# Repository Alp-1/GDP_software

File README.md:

This project aims to develop a rover that can navigate through different terrain in a forest environment autonomously.
The wiki containing more informatin about the rover can be found [here](https://github.com/Alp-1/NANA-Forest-Rover/wiki).

A more detailed account of the development process can be found [here](https://alportakci.com/projects/).

## The directory layout

    .
    ├── .vscode                 # VS Code settings
    ├── CAD Models              # CAD Models used in the project with attributions. 
    ├── ESP32                   # ESP32 code for ESP32-C3 dronebridge.
    ├── GPS                     # Script to start NTRIP caster.
    ├── low_level_control       # Low level control
    ├── lua_scripts             # Lua scripts uploaded in flight controller
    ├── navigation              # Autonomous navigation
    ├── pyrealsense             # Intel Realsense library required on Raspberry Pi
    ├── schematic               # Schematic of the low level controller
    ├── .gitignore
    ├── pyproject.toml          # Python dependencies
    └── README.md

### Installation
To run some code that are not hardware dependent on your local PC, you can run the following commands in Python (Version used: **3.10.5** in PC and Raspberry Pi):

(./ is the repo root directory)
```sh
$ pip install -e .
```

## Low Level Control
There are two components in the low level control i.e. the motor controller and the central hub. They are both implemented on the Raspberry Pi Pico using micropython. See the [README.md](low_level_control/README.md) in the low level control folder for more information.

## Autonomous navigation
The files in the pyrealsense folder may have to be in the same directory as the navigation scripts, depending on your installation.
Another option is to include the right package from local directory i.e. 
```python
from pyrealsense import pyrealsense2 as rs
``` 
To run the autonomous navigation script, use the following command in the navigation folder:
```sh
$ python navigation_final.py
```
## Research Poster

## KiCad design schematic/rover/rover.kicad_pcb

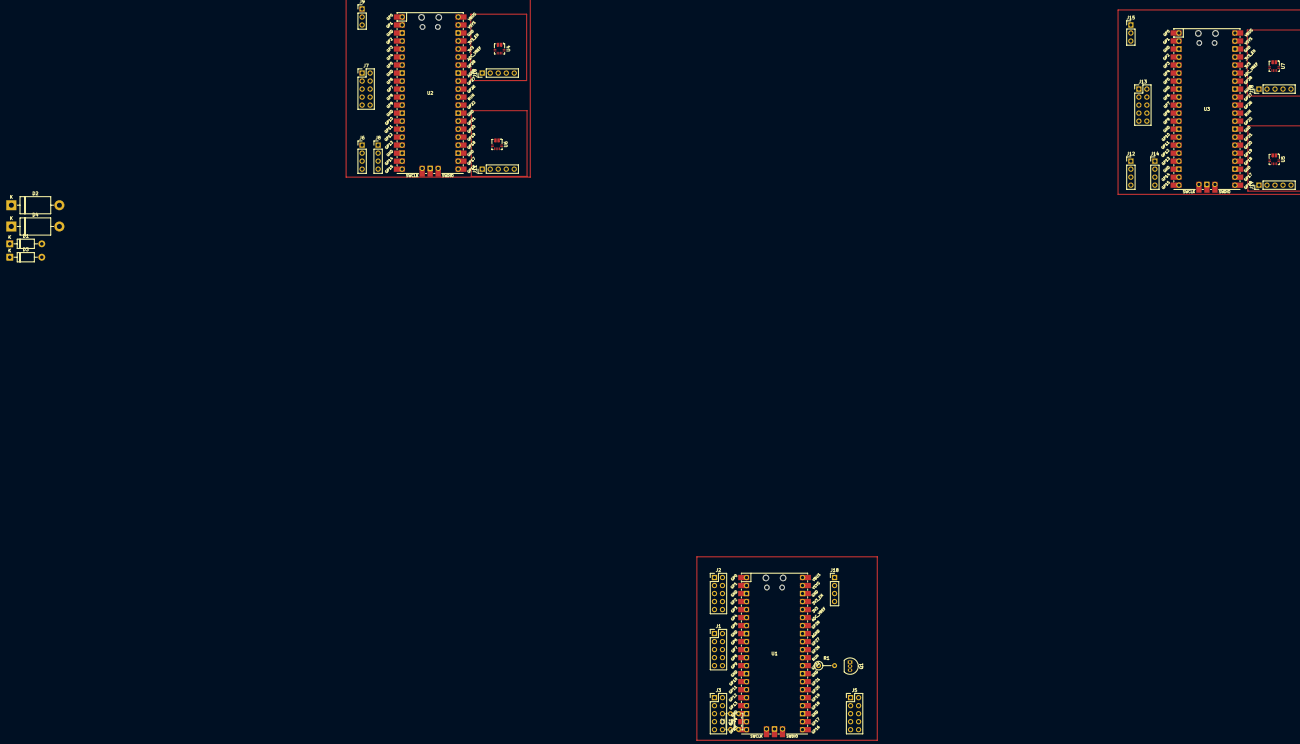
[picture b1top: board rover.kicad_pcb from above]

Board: 2 copper layers, 32 parts (0 on the bottom side), 34 nets, no tracks yet.

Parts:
C1, C2: 3.3n; C_Disc_D5.0mm_W2.5mm_P5.00mm
D1, D3: 1N4733A; D_DO-41_SOD81_P10.16mm_Horizontal
D2, D4: 1N5820; D_DO-201AD_P15.24mm_Horizontal
J1: Front_Wheel_Conn; PinHeader_2x05_P2.54mm_Vertical
J2: Rear_Wheel_Conn; PinHeader_2x05_P2.54mm_Vertical
J3: Flight_Controller_Conn; PinHeader_2x05_P2.54mm_Vertical
J5: Receiver_Conn; PinHeader_2x05_P2.54mm_Vertical
J6, J12: Left_Encoder; PinHeader_1x04_P2.54mm_Vertical
J7, J13: Conn_02x05_Odd_Even; PinHeader_2x05_P2.54mm_Vertical
J8, J14: Right_Encoder; PinHeader_1x04_P2.54mm_Vertical
J9, J15: Conn_01x03_Socket; PinHeader_1x03_P2.54mm_Vertical
J10, J16: Right_Current_Sense; PinHeader_1x05_P2.54mm_Vertical
J11, J17: Left_Current_Sense; PinHeader_1x05_P2.54mm_Vertical
J18: Conn_01x04_Socket; PinHeader_1x04_P2.54mm_Vertical
Q1: BC547; TO-92_Inline
R1: 100k; R_Axial_DIN0207_L6.3mm_D2.5mm_P5.08mm_Vertical
U1, U2, U3: Pico; RPi_Pico_SMD_TH
U4, U5, U6, U7: ACS711xEXLT-31AB; Allegro_QFN-12-10-1EP_3x3mm_P0.5mm

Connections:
+3.3V: J5.3, J6.3, J8.3, J10.3, J11.3, J12.3, J14.3, J16.3, J17.3, U1.36 (3V3), U2.36 (3V3), U3.36 (3V3), U4.10 (VCC), U5.10 (VCC), U6.10 (VCC), U7.10 (VCC)
+5V: J9.1, J15.1, J18.2, U1.39 (VSYS)
/low level control/+5V_in: D2.1 (K), U2.39 (VSYS), U3.39 (VSYS)
/low level control/Sabertooth_front/S1: J9.2, U2.1 (GPIO0)
/low level control/Sabertooth_front/S2: J18.4, Q1.1 (C)
/low level control/Sabertooth_rear/S1: J15.2, U3.1 (GPIO0)
/low level control/central_hub/FC__SBUS: J3.1, J5.1
/low level control/central_hub/FC__Throttle_Left: C1.1, J3.8, U1.19 (GPIO14)
/low level control/central_hub/FC__Throttle_Right: C2.1, J3.10, U1.20 (GPIO15)
/low level control/central_hub/Flight_Controller__RX: J3.7, U1.22 (GPIO17)
/low level control/central_hub/Flight_Controller__TX: J3.9, U1.21 (GPIO16)
/low level control/central_hub/Front_Controller__RX: J1.8, J7.8, U1.2 (GPIO1), U2.6 (GPIO4)
/low level control/central_hub/Front_Controller__TX: J1.10, J7.10, U1.1 (GPIO0), U2.7 (GPIO5)
/low level control/central_hub/NeoPixelRGB: J18.1, U1.32 (GPIO27_ADC1)
/low level control/central_hub/OUTA_Left__Front: J1.7, J6.4, J7.7, U1.7 (GPIO5), U2.16 (GPIO12)
/low level control/central_hub/OUTA_Left__Rear: J2.7, J3.3, J12.4, J13.7, U1.14 (GPIO10), U3.16 (GPIO12)
/low level control/central_hub/OUTA_Right__Front: J1.6, J7.6, J8.4, U1.5 (GPIO3), U2.20 (GPIO15)
/low level control/central_hub/OUTA_Right__Rear: J2.6, J3.4, J13.6, J14.4, U1.17 (GPIO13), U3.20 (GPIO15)
/low level control/central_hub/OUTB_Left__Front: J1.9, J6.1, J7.9, U1.6 (GPIO4), U2.17 (GPIO13)
/low level control/central_hub/OUTB_Left__Rear: J2.9, J3.5, J12.1, J13.9, U1.15 (GPIO11), U3.17 (GPIO13)
/low level control/central_hub/OUTB_Right__Front: J1.4, J7.4, J8.1, U1.4 (GPIO2), U2.19 (GPIO14)
/low level control/central_hub/OUTB_Right__Rear: J2.4, J3.2, J13.4, J14.1, U1.16 (GPIO12), U3.19 (GPIO14)
/low level control/central_hub/Rear_Controller__RX: J2.8, J13.8, U1.12 (GPIO9), U3.6 (GPIO4)
/low level control/central_hub/Rear_Controller__TX: J2.10, J13.10, U1.11 (GPIO8), U3.7 (GPIO5)
/low level control/central_hub/Receiver__PPM: J5.2, U1.27 (GPIO21)
/power supply/5V_RaspberryPi: D3.1 (K), D4.2 (A)
GND: C1.2, C2.2, D1.2 (A), D3.2 (A), J1.2, J2.2, J3.6, J5.5, J6.2, J7.2, J8.2, J9.3, J10.1, J10.2, J11.1, J11.2, J12.2, J13.2, J14.2, J15.3, J16.1, J16.2, J17.1, J17.2, J18.3, Q1.3 (E), U1.3 (GND), U1.8 (GND), U1.13 (GND), U1.18 (GND), U1.23 (GND), U1.28 (GND), U1.38 (GND), U2.3 (GND), U2.18 (GND), U2.23 (GND), U2.28 (GND), U2.38 (GND), U3.3 (GND), U3.18 (GND), U3.23 (GND), U3.28 (GND), U3.38 (GND), U4.3 (GND), U5.3 (GND), U6.3 (GND), U7.3 (GND)
unnamed: D1.1 (K), D2.2 (A)
unnamed: J10.4, U2.32 (GPIO27_ADC1), U6.9 (VIOUT)
unnamed: J11.4, U2.34 (GPIO28_ADC2), U4.9 (VIOUT)
unnamed: J16.4, U3.32 (GPIO27_ADC1), U7.9 (VIOUT)
unnamed: J17.4, U3.34 (GPIO28_ADC2), U5.9 (VIOUT)
unnamed: Q1.2 (B), R1.2
unnamed: R1.1, U1.29 (GPIO22)

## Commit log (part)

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2023-10-30 encoder
2023-11-08 added basic depth based obstacle avoidance
2023-11-10 Motor controller
2023-11-20 Update 2 files
    - /GPS/gnssapp.py
    - /GPS/messntripcomms.py
2023-11-22 Copy dronebridge repo from https://github.com/DroneBridge/ESP32
2023-11-22 Changes to the code to establish serail over UART on ESP32C3
    Changes to the UART port (2 ->1), changes to the proxy, "1604",
2023-11-22 Rebuilding the project
2023-11-22 Changes to the UART pin assignment, to receive information flight controller
2023-11-24 added a simple version of the obstacle avoidance algorithm
2023-11-26 debugging navigation integration
2023-11-26 override rc channels
2023-11-27 commented out things
2023-11-28 added data collection script
2023-12-03 changed the camera settings to reduce motion blur
2023-12-03 changed camera settings for steering
2023-12-03 mode switching
2023-12-03 bugfixing
2023-12-04 fuck
2023-12-04 Add some essential mavlink message handler to give:
    - voltage
    - current
    - speed
    - encode,current data from pico
2023-12-05 Enable current readings from pico to Flight controller
    - Refactor communication methods between cntral hub and controller to use the standardised protocol
2023-12-05 Add standardised protocol for interpico comms
    - Required to allow current values to be passed between picos
2023-12-05 Update tests to use the latest protocols
2023-12-05 Add Software serial class
    - Required for communication with FC as exsiting 2 uarts are insufficient
2023-12-05 Add limits for negative values coming from pulse timeout
2023-12-05 Update code for stripboard layout
    - Receiver - Changed for more compact layout
    - Central_UART -Changed due to GND shorted with 8/9 pin pair
2023-12-05 Fix uart bug in mavlite that initialises with default pin
2023-12-05 Add mavlink library from MavLite
    - Add upy_mavlink package
2023-12-05 Refactor protocol.py
    - Update the protocol with the latest set of command types
    - Make protocol more robust by accumulating and slicing data instead of hoping for timing sync
    - Creates two buffer as central hub requires two sets of separate buffer for messages coming from front and rear
2023-12-05 Refactor motor_controller
    - Remove handshake together with the changes in central_hub
    - Add constant sensor data broadcast methods
    - Commented out pid as it is not stable yet
2023-12-05 Chnage central_hub to match latest mavlink implementation
    - Use asyncio for main loop in central hub
    - Respond to sensor data instead of requesting them to reduce chances of failure
    - Scrape handshake wait as it does not contribute much at the moment
    - The driver can be put to disable by just sending drive(0,0) or e-stop
2023-12-05 Reduce baudrate for softuart to reduce the load on pico
    - Reduce the lost packets as well
2023-12-05 Allow PID to be stopped in deadzone
    - Further tune PID constants for period of 200ms
2023-12-05 Replace Exception with bounded input
2023-12-05 Add methods to check the status of receiver and encoder
2023-12-05 Remove exit fault code as the state is updated in parse_command
2023-12-05 Increase the pulse timeout for pwm
    - Ensure the pulse is captured by the pico
2023-12-05 Update hardware change in the pins
    - The estop becomes active high because of the transistor switching circuit
2023-12-05 Make speed and turn input reversible in direct rc mode
2023-12-05 Prevent hardware interrupt firing before memory allocation
2023-12-05 Refactor state handler to configure state in parse command
2023-12-05 Increase sensor update rate, pid output range and deadzone
    - Fix typo and remove unused code
2023-12-05 Modify PPR
    - Formula: gear ratio * motor PPR * 4 (51*12*4=2448)
2023-12-05 added simple avoidance for testing
2023-12-05 what
2023-12-05 final testing
2023-12-05 Implement clipping output instead of driving to 0 immediately
    - Avoid issue that might damage the gearbox if the output oscillates between 0-100
2023-12-05 Remove unused code and flag
2023-12-05 Move low level codes into a separate folder
2023-12-05 mavlink debugging
2023-12-05 giving time for the rover to turn
2023-12-07 Combine the tests into one directory
    - Allow discovery of the low_level_control at root level pyproject.toml
2023-12-07 Refactor central hub
    - Split various update methods
    - Remove unused code
    - Split send mavlink code into separate method
    - Simplify timing in main command loop
    - Remove unused tests
2023-12-07 Allow reversible autonomous output
2023-12-07 Fix bug in output_map method
2023-12-07 Attempt to make mavlink params non-blocking
2023-12-07 steering tuning
2023-12-07 Fix missing message issue
    - Wait for the message using recv_match for a maximum of timeout second
2023-12-07 Allow additional conditions for mavlink messages from pico
2023-12-07 Fix flight controller mode function
2023-12-08 Filter heartbeat from rover only
2023-12-08 testing open3d
2023-12-08 open3d...
2023-12-08 Allow user to flush serial input buffer
    - To get the latest mavlink packet
2023-12-08 pointcloud creation
2023-12-09 ok :)
2023-12-09 plane segmentation testing
2023-12-09 Automatic ACM selection messntripcomms.py
2023-12-10 cleanup, improved clear path choice
2023-12-10 added plane grid
2023-12-11 hole filling filter, obstacle detection
2023-12-11 added threshold filter to the depth image
2023-12-13 small fix
2023-12-14 added different versions of steering to test mavlink commands
2023-12-15 added logging to avoidance script
2023-12-15 post processing filters applied to depth image
2023-12-16 restructuring, storing slope grid
2023-12-18 implemented deadend detection, increased rover speed slightly
2023-12-18 added script for testing without mavlink
2023-12-18 added hole filling to spatial filter, distance calculation from depth image
2023-12-18 test
2023-12-18 only fit plane if cell has at least 10 points
2023-12-18 added function to measure to size of the gap for chosen direction
2023-12-18 more debugging
2023-12-18 show rgb image
2023-12-18 debugging...
2023-12-18 changed obstacle threshold
2023-12-18 increased sleep time between mavlink commands
2023-12-19 get the latest frames from camera
2023-12-19 Fix motor id and rotation direction at low level
    - Ensure that it is consistent wih the motor wiring
2023-12-19 Allow motor controller to parse all messages in buffer
    - Prevent out of sync movement between front and rear wheels
2023-12-19 Add more print to pid test method
2023-12-19 Ensure the correctness of current measurement
    - Forward gives positive current and vice versa
    - Add invert_current argument to Sensor class
2023-12-19 added gap measurement, decreased downward obstacle detection
2023-12-19 gap size measurement fix
2023-12-19 avoidance.py updates
2023-12-19 parameter tuning
2023-12-19 different mavlink command options
2023-12-19 added navigation.py for navigation with AUTO mode
2023-12-20 changed movement commands
2023-12-20 deadend debugging
2023-12-20 testing tall vegetation and collision detection
2023-12-20 Add wheel distance getter
2023-12-20 Remove unnecessary rc override
2023-12-20 Add hysteresis to prevent going from 0 to full speed in one iteration
2023-12-20 Simplify detect mode change method
2023-12-20 Add disconnect timeout from central pico
2023-12-20 Add missing await for sending sensor data
2023-12-20 Remove unused command
2023-12-20 Update tests
2023-12-20 deadend sanity check
2023-12-20 Add RC disconnect failsafe in low level controller
2023-12-20 changed deadend threshold, implemented collision and tall vegetation detection
2023-12-20 typo lol
2023-12-21 reduced guided speed, parameter tuning, add gap size to manual script for testing
2023-12-21 gap size improvements, updated navigation.py
2023-12-21 gap fix
2023-12-22 increased rgb gain, set threshold filter to 4m to ignore variation in background for steering
2023-12-22 Add logging with time for avoidance.py
2023-12-23 parameter tuning, data collection update
2023-12-23 sorry
2023-12-24 added logging to navigation.py
2023-12-24 logging
2023-12-25 Fix logging issue
2023-12-26 Remove vehicle object from navigation
2023-12-30 added flipping detection
2023-12-30 getting IMU data with mav_listener
2024-01-05 added slope grid with rotation
2024-01-05 get_slope_grid not returning pcds anymore
2024-01-05 added thresholded image for furthest away direction calculation
2024-01-05 added semantic segmentation
2024-01-05 cleanup
2024-01-05 added script for testing
2024-01-05 added models
2024-01-05 quick fix
2024-01-05 5 minutes 5 minutes
2024-01-05 Update messntripcomms.py
    Timeout 30
    gga message every 5m secs
2024-01-05 Try GPS_INPUT instead of GPS_RAW_INT
2024-01-05 Add a send fakegps function
2024-01-05 Add default values for fake gps
2024-01-05 Add functions to switch between different gps types
2024-01-05 Add message interval control function
2024-01-05 new obstacle distance
2024-01-05 masked 0's
2024-01-05 print slope
2024-01-05 print angle
2024-01-06 Rename motor.py
2024-01-06 more debugging yay so fun
2024-01-06 notation
2024-01-06 yeah
2024-01-06 yeahyeah
2024-01-06 points
2024-01-06 Rename methods
    - Tidy up
2024-01-06 reduced slope to 4 columns
2024-01-06 sexy
2024-01-06 new dist
2024-01-06 smal mistake
2024-01-07 integration
2024-01-07 not sure
2024-01-07 Change serial port on FC
    - UART on rpi5 doesnt work out of the box
2024-01-07 dist to obst
2024-01-07 Rename serial0 to ttyAMA0
    - In rpi5 serial0 points to the UART connector instead
    - See https://forums.raspberrypi.com/viewtopic.php?p=2176627#p2176529
2024-01-07 lmao
2024-01-07 Allow drive backwards manually
    - Not the most opitimal implementation
2024-01-08 fixed slope return
2024-01-08 mask shape
2024-01-08 resize mask to fit depth image shape
2024-01-08 testing direction execution time
2024-01-08 Fix missing argument
2024-01-08 Round pwm to integer
2024-01-08 set correct sigma values for semantic
2024-01-08 new closest point calculation
2024-01-08 added collision detection, going back
2024-01-08 oops
2024-01-08 terrain ahead
2024-01-08 time
2024-01-08 terrain analysis
2024-01-08 small mistake
2024-01-08 final fix
2024-01-08 sada
2024-01-09 collision:
2024-01-09 changes in the forest
2024-01-10 testing
2024-01-10 disparity shift
2024-01-10 Rename for less confusing names
2024-01-11 lower res
2024-01-11 removed other decision
2024-01-11 changed back command
2024-01-11 Move low level documentation
2024-01-11 remove unused import
2024-01-11 Add lua scripts used in project
2024-01-15 stopped aligning, reduced speed threshold for tall vegetation, only 1 cases possible/frame
2024-01-15 removed slope grid prints
2024-01-15 added back command
2024-01-15 changed collision threshold speed
2024-01-15 it kinda works yay
2024-01-17 changed mavlink frequency
2024-01-17 removed mavlink command
2024-01-17 back command and collision testing
2024-01-17 changed timeout
2024-01-18 fixed going back command
2024-01-18 switch to AUTO before navigation for initial alignment towards the waypoint. added for completeness and my sanity
2024-01-29 Add deadend getter functions
2024-01-29 cleaned up code a bit
2024-01-29 added folders
2024-01-29 readme for navigation
2024-01-29 readme clarification
2024-01-29 Complete motor controller schematic
2024-01-29 Initial commit
    - Includes pico library from https://github.com/ncarandini/KiCad-RP-Pico
    - Some schematic on motor controller around pico
2024-01-29 Update connection between picos
2024-01-29 Complete power board and motor wiring
2024-01-29 Complete Central Hub schematic
2024-01-29 Arrange components following the stripboard layout
2024-01-29 Remove cache and preference file
2024-01-29 Allow pytest in vscode
2024-01-29 Increase uncapped current threshold
2024-01-29 Remove unused files
2024-01-29 Allow auto-discovery for low-level-control
    - Move pyproject.toml back to root level
    - Remove typo
2024-01-29 Move protocol.py into low level controller
2024-01-29 Remove unused code
2024-01-29 Add more documentations
2024-02-01 Remove unused data folder
2024-02-02 Add link to Wiki page
2024-02-02 Update README.md - Remove typo
2024-07-16 Rover localisation and minor fixes
